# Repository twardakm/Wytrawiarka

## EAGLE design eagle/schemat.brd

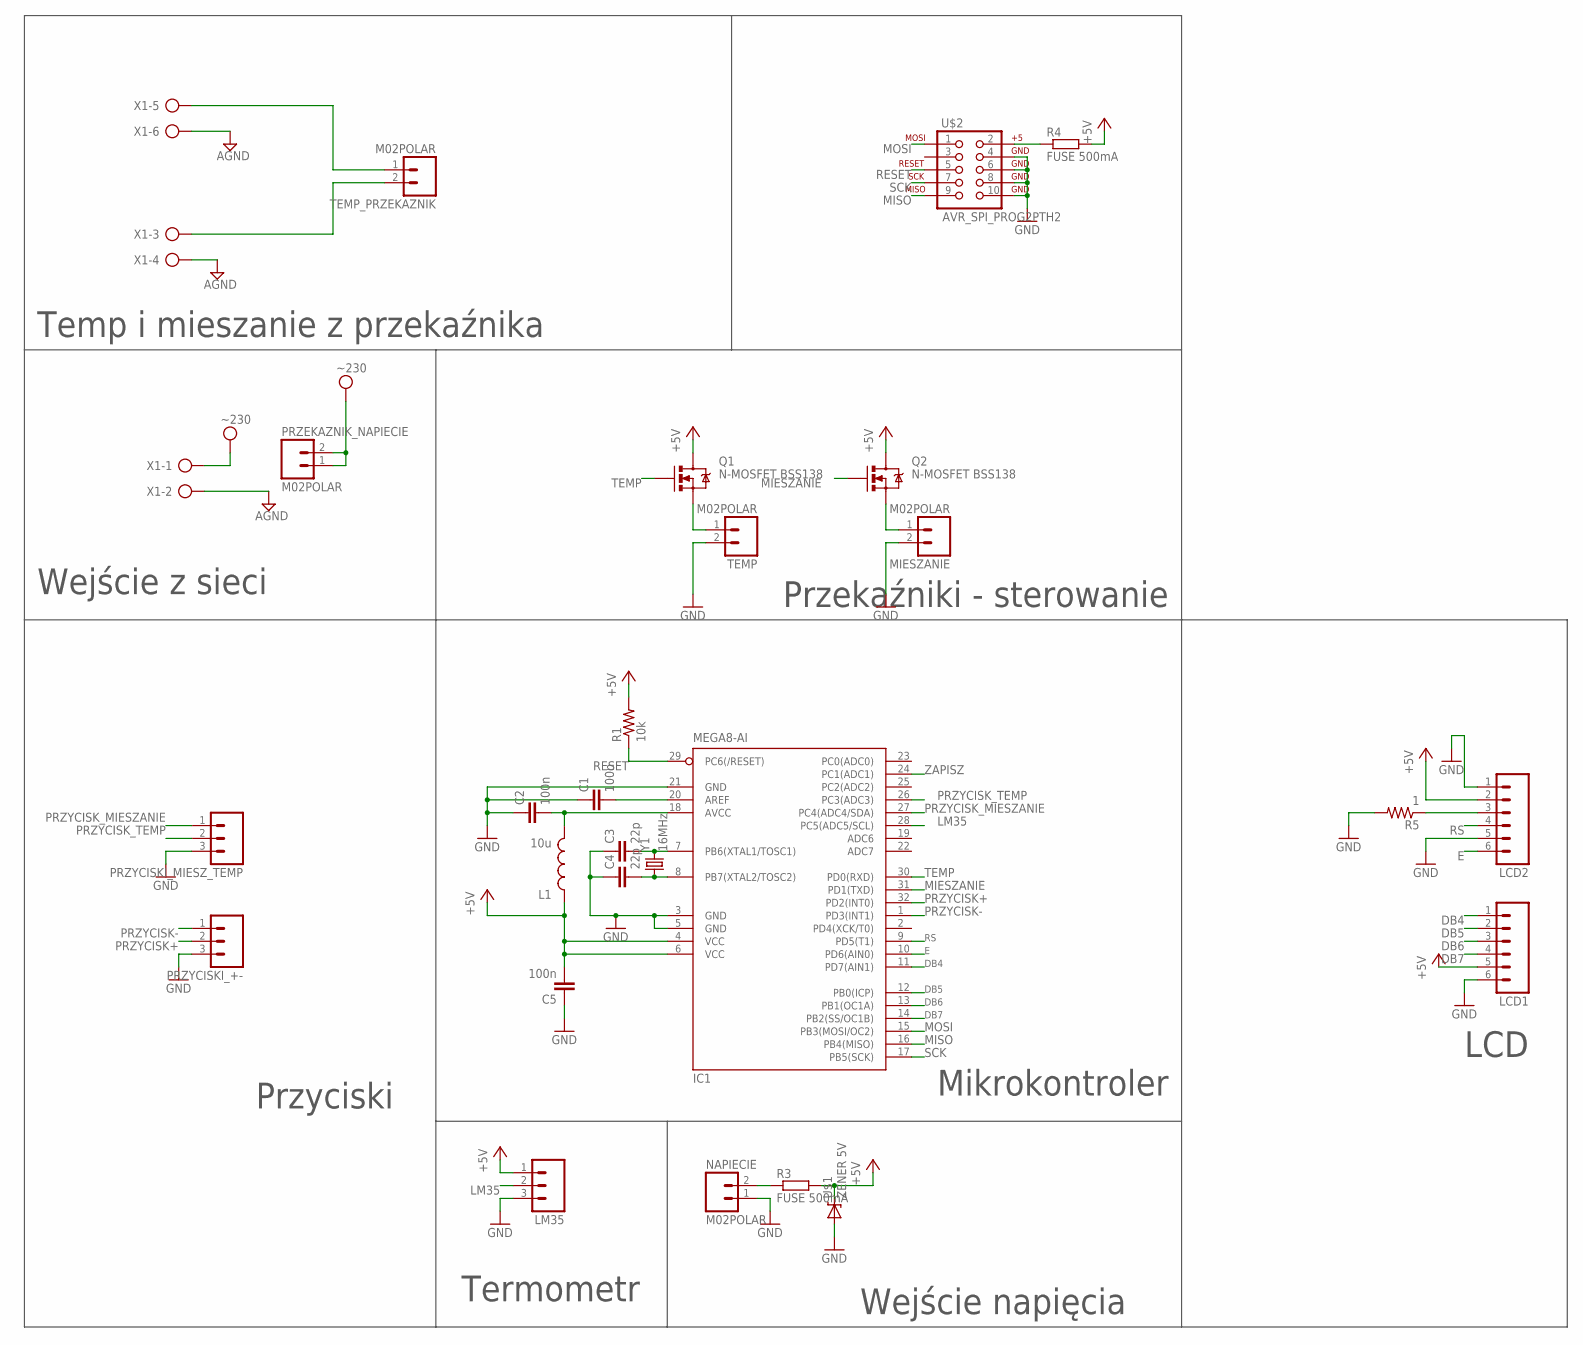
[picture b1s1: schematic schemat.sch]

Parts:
C1, C2, C5: 100n; 0805
C3, C4: 22p; 0805
IC1: MEGA8-AI; TQFP32-08
L1: 10u; 0805
LCD1, LCD2: M06POLAR; MOLEX-1X6
LM35: M03POLAR; MOLEX-1X3
MIESZANIE: M02POLAR; MOLEX-1X2
NAPIECIE: M02POLAR; MOLEX-1X2
PRZEKAZNIK_NAPIECIE: M02POLAR; MOLEX-1X2
PRZYCISKI_+-: M03POLAR; MOLEX-1X3
PRZYCISKI_MIESZ_TEMP: M03POLAR; MOLEX-1X3
Q1, Q2: N-MOSFET BSS138; SOT23
R1: 10k; 0805
R3, R4: FUSE 500mA; M0805
R5: 1; 0805
TEMP: M02POLAR; MOLEX-1X2
TEMP_PRZEKAZNIK: M02POLAR; MOLEX-1X2
U$1: ZENER 5V; SMB-DIODE
U$2: AVR_SPI_PROG2PTH2; 2X5-SHROUDED
X1: AK300/6
Y1: 16MHz; HC49US

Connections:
+5V: C5.2, IC1.4 (VCC), IC1.6 (VCC), L1.1, LCD1.5, LCD2.2, LM35.1, Q1.3 (D), Q2.3 (D), R1.2, R3.2, R4.2, U$1.C
AGND: X1.2, X1.4, X1.6
DB4: IC1.11 (PD7(AIN1)), LCD1.1
DB5: IC1.12 (PB0(ICP)), LCD1.2
DB6: IC1.13 (PB1(OC1A)), LCD1.3
DB7: IC1.14 (PB2(SS/OC1B)), LCD1.4
E: IC1.10 (PD6(AIN0)), LCD2.6
GND: C1.1, C2.1, C3.1, C4.1, C5.1, IC1.3 (GND), IC1.5 (GND), IC1.21 (GND), LCD1.6, LCD2.1, LCD2.5, LM35.3, MIESZANIE.2, NAPIECIE.1, PRZYCISKI_+-.3, PRZYCISKI_MIESZ_TEMP.3, R5.2, TEMP.2, U$1.A, U$2.4, U$2.6, U$2.8, U$2.10
LM35: IC1.28 (PC5(ADC5/SCL)), LM35.2
MIESZANIE: IC1.31 (PD1(TXD)), Q2.1 (G)
MISO: IC1.16 (PB4(MISO)), U$2.9
MOSI: IC1.15 (PB3(MOSI/OC2)), U$2.1
unnamed: C2.2, IC1.18 (AVCC), L1.2
unnamed: C1.2, IC1.20 (AREF)
unnamed: Q1.2 (S), TEMP.1
unnamed: MIESZANIE.1, Q2.2 (S)
unnamed: C4.2, IC1.8 (PB7(XTAL2/TOSC2)), Y1.1
unnamed: C3.2, IC1.7 (PB6(XTAL1/TOSC1)), Y1.2
unnamed: NAPIECIE.2, R3.1
unnamed: TEMP_PRZEKAZNIK.2, X1.3
unnamed: R4.1, U$2.2
unnamed: TEMP_PRZEKAZNIK.1, X1.5
unnamed: LCD2.3, R5.1
PRZYCISK+: IC1.32 (PD2(INT0)), PRZYCISKI_+-.2
PRZYCISK-: IC1.1 (PD3(INT1)), PRZYCISKI_+-.1
PRZYCISK_MIESZANIE: IC1.27 (PC4(ADC4/SDA)), PRZYCISKI_MIESZ_TEMP.1
PRZYCISK_TEMP: IC1.26 (PC3(ADC3)), PRZYCISKI_MIESZ_TEMP.2
RESET: IC1.29 (PC6(/RESET)), R1.1, U$2.5
RS: IC1.9 (PD5(T1)), LCD2.4
SCK: IC1.17 (PB5(SCK)), U$2.7
TEMP: IC1.30 (PD0(RXD)), Q1.1 (G)
VDD: PRZEKAZNIK_NAPIECIE.1, PRZEKAZNIK_NAPIECIE.2, X1.1
ZAPISZ: IC1.24 (PC1(ADC1))

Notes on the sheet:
Mikrokontroler
LCD
Termometr
Przyciski
Przekaźniki - sterowanie
Wejście napięcia
Wejście z sieci
Temp i mieszanie z przekaźnika

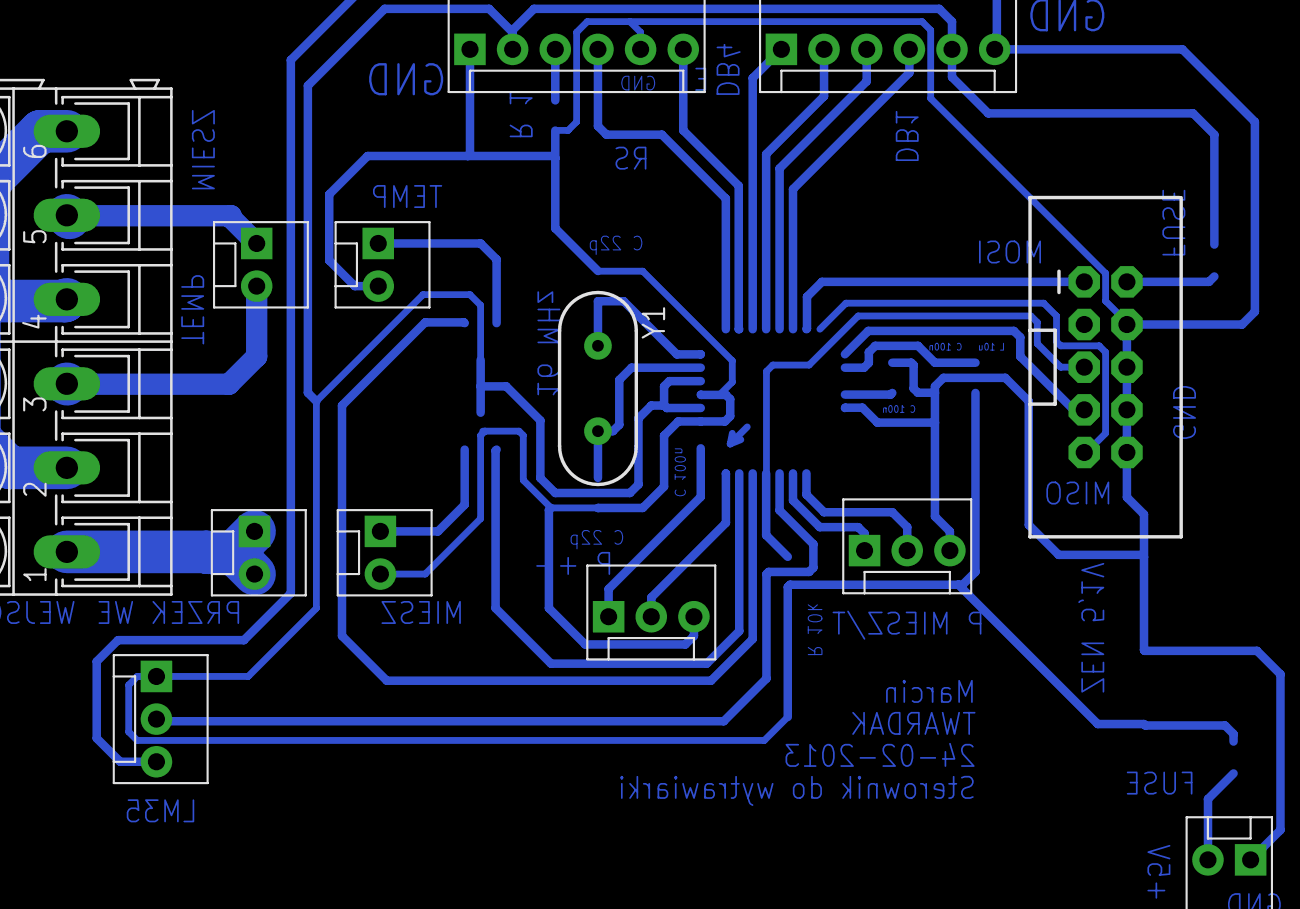
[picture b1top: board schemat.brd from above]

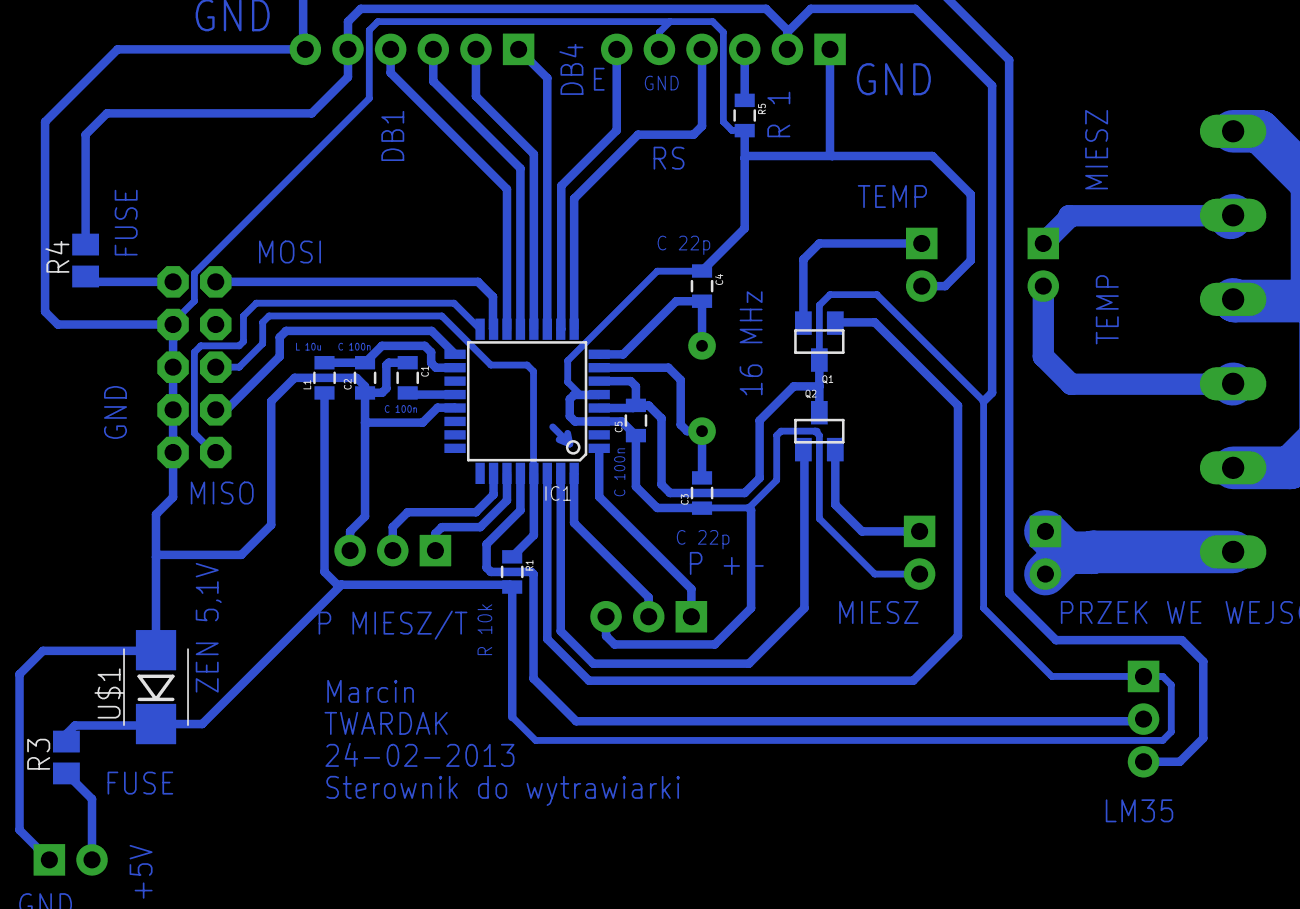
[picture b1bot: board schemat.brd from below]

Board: 2 copper layers, 27 parts (14 on the bottom side), 32 nets.

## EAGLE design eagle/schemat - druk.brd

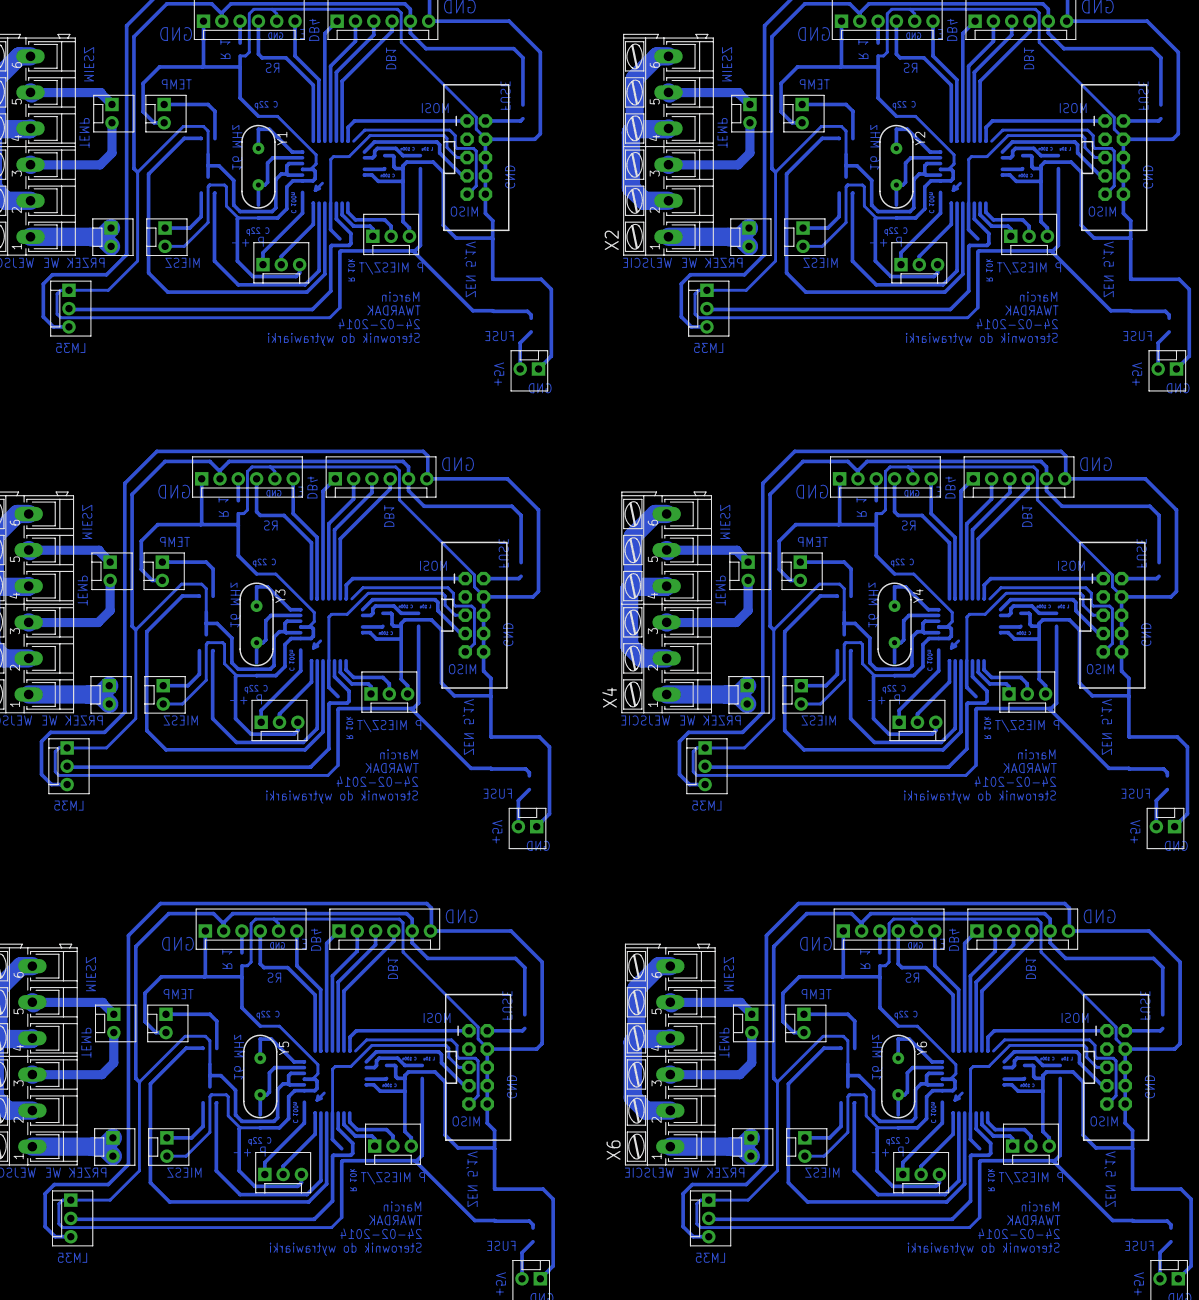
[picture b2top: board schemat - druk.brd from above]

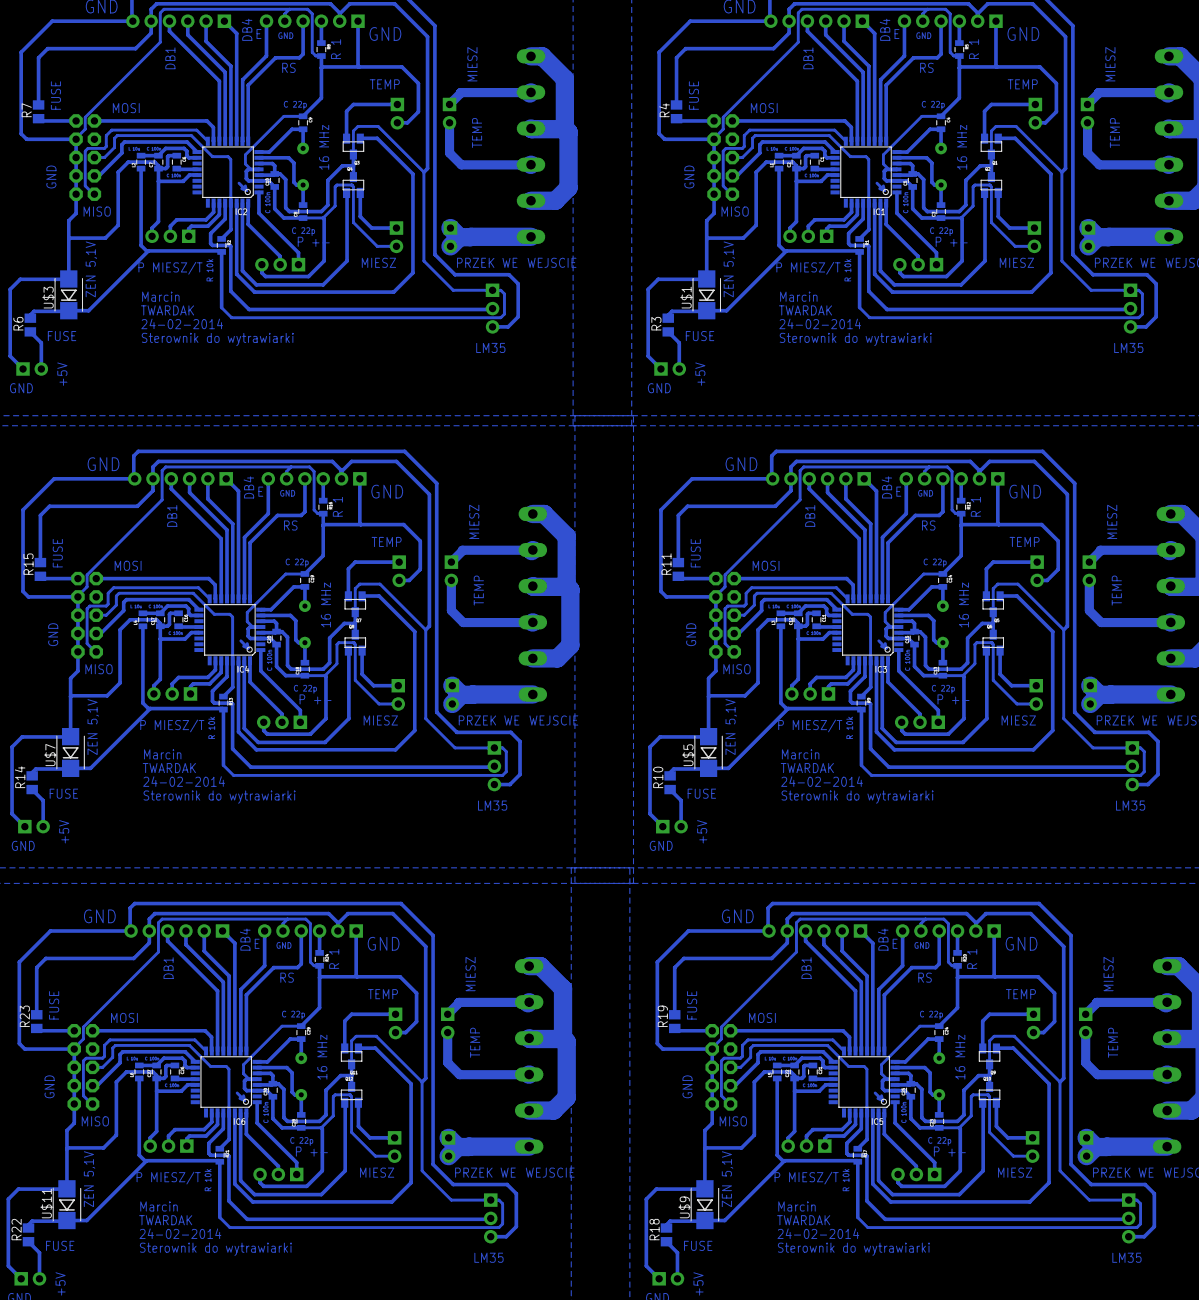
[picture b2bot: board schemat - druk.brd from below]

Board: 2 copper layers, 162 parts (84 on the bottom side), 192 nets.

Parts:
C1, C2, C5, C6, C7, C10, C11, C12, C15, C16, C17, C20, C21, C22, C25, C26, C27, C30: 100n; 0805
C3, C4, C8, C9, C13, C14, C18, C19, C23, C24, C28, C29: 22p; 0805
IC1, IC2, IC3, IC4, IC5, IC6: MEGA8-AI; TQFP32-08
L1, L2, L3, L4, L5, L6: 10u; 0805
LCD1, LCD2, LCD3, LCD4, LCD5, LCD6, LCD7, LCD8, LCD9, LCD10, LCD11, LCD12: MOLEX-1X6
LM1, LM2, LM3, LM4, LM5, LM35: MOLEX-1X3
MIESZANIE, MIESZANIE1, MIESZANIE2, MIESZANIE3, MIESZANIE4, MIESZANIE5: M02POLAR; MOLEX-1X2
NAPIECIE, NAPIECIE1, NAPIECIE2, NAPIECIE3, NAPIECIE4, NAPIECIE5: M02POLAR; MOLEX-1X2
PRZEKAZNIK_NAPIECIE, PRZEKAZNIK_NAPIECIE1, PRZEKAZNIK_NAPIECIE2, PRZEKAZNIK_NAPIECIE3, PRZEKAZNIK_NAPIECIE4, PRZEKAZNIK_NAPIECIE5: M02POLAR; MOLEX-1X2
PRZYCISKI_+-, PRZYCISKI_+-1, PRZYCISKI_+-2, PRZYCISKI_+-3, PRZYCISKI_+-4, PRZYCISKI_+-5: MOLEX-1X3
PRZYCISKI_MIESZ_TEMP, PRZYCISKI_MIESZ_TEMP1, PRZYCISKI_MIESZ_TEMP2, PRZYCISKI_MIESZ_TEMP3, PRZYCISKI_MIESZ_TEMP4, PRZYCISKI_MIESZ_TEMP5: MOLEX-1X3
Q1, Q2, Q3, Q4, Q5, Q6, Q7, Q8, Q9, Q10, Q11, Q12: N-MOSFET BSS138; SOT23
R1, R2, R9, R13, R17, R21: 10k; 0805
R3, R4, R6, R7, R10, R11, R14, R15, R18, R19, R22, R23: FUSE 500mA; M0805
R5, R8, R12, R16, R20, R24: 1; 0805
TEMP, TEMP1, TEMP2, TEMP3, TEMP4, TEMP5: M02POLAR; MOLEX-1X2
TEMP_PRZEKAZNIK, TEMP_PRZEKAZNIK1, TEMP_PRZEKAZNIK2, TEMP_PRZEKAZNIK3, TEMP_PRZEKAZNIK4, TEMP_PRZEKAZNIK5: M02POLAR; MOLEX-1X2
U$1, U$3, U$5, U$7, U$9, U$11: ZENER 5V; SMB-DIODE
U$2, U$4, U$6, U$8, U$10, U$12: AVR_SPI_PROG2PTH2; 2X5-SHROUDED
X1, X2, X3, X4, X5, X6: AK300/6
Y1, Y2, Y3, Y4, Y5, Y6: 16MHz; HC49US

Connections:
+5V: C5.2, IC1.4, IC1.6, L1.1, LCD1.5, LCD2.2, LM35.1, Q1.3, Q2.3, R1.2, R3.2, R4.2, U$1.C
+5V1: C10.2, IC2.4, IC2.6, L2.1, LCD3.5, LCD4.2, LM1.1, Q3.3, Q4.3, R2.2, R6.2, R7.2, U$3.C
+5V2: C15.2, IC3.4, IC3.6, L3.1, LCD5.5, LCD6.2, LM2.1, Q5.3, Q6.3, R9.2, R10.2, R11.2, U$5.C
+5V3: C20.2, IC4.4, IC4.6, L4.1, LCD7.5, LCD8.2, LM3.1, Q7.3, Q8.3, R13.2, R14.2, R15.2, U$7.C
+5V4: C25.2, IC5.4, IC5.6, L5.1, LCD9.5, LCD10.2, LM4.1, Q9.3, Q10.3, R17.2, R18.2, R19.2, U$9.C
+5V5: C30.2, IC6.4, IC6.6, L6.1, LCD11.5, LCD12.2, LM5.1, Q11.3, Q12.3, R21.2, R22.2, R23.2, U$11.C
AGND: X1.2, X1.4, X1.6
AGND1: X2.2, X2.4, X2.6
AGND2: X3.2, X3.4, X3.6
AGND3: X4.2, X4.4, X4.6
AGND4: X5.2, X5.4, X5.6
AGND5: X6.2, X6.4, X6.6
DB1: IC2.11, LCD3.1
DB2: IC2.12, LCD3.2
DB3: IC2.13, LCD3.3
DB4: IC1.11, LCD1.1
DB5: IC1.12, LCD1.2
DB6: IC1.13, LCD1.3
DB7: IC1.14, LCD1.4
DB8: IC2.14, LCD3.4
DB9: IC3.11, LCD5.1
DB10: IC3.12, LCD5.2
DB11: IC3.13, LCD5.3
DB12: IC3.14, LCD5.4
DB13: IC4.11, LCD7.1
DB14: IC4.12, LCD7.2
DB15: IC4.13, LCD7.3
DB16: IC4.14, LCD7.4
DB17: IC5.11, LCD9.1
DB18: IC5.12, LCD9.2
DB19: IC5.13, LCD9.3
DB20: IC5.14, LCD9.4
DB21: IC6.11, LCD11.1
DB22: IC6.12, LCD11.2
DB23: IC6.13, LCD11.3
DB24: IC6.14, LCD11.4
E: IC1.10, LCD2.6
E1: IC2.10, LCD4.6
E2: IC3.10, LCD6.6
E3: IC4.10, LCD8.6
E4: IC5.10, LCD10.6
E5: IC6.10, LCD12.6
GND: C1.1, C2.1, C3.1, C4.1, C5.1, IC1.3, IC1.5, IC1.21, LCD1.6, LCD2.1, LCD2.5, LM35.3, MIESZANIE.2, NAPIECIE.1, PRZYCISKI_+-.3, PRZYCISKI_MIESZ_TEMP.3, R5.2, TEMP.2, U$1.A, U$2.4, U$2.6, U$2.8, U$2.10
GND1: C6.1, C7.1, C8.1, C9.1, C10.1, IC2.3, IC2.5, IC2.21, LCD3.6, LCD4.1, LCD4.5, LM1.3, MIESZANIE1.2, NAPIECIE1.1, PRZYCISKI_+-1.3, PRZYCISKI_MIESZ_TEMP1.3, R8.2, TEMP1.2, U$3.A, U$4.4, U$4.6, U$4.8, U$4.10
GND2: C11.1, C12.1, C13.1, C14.1, C15.1, IC3.3, IC3.5, IC3.21, LCD5.6, LCD6.1, LCD6.5, LM2.3, MIESZANIE2.2, NAPIECIE2.1, PRZYCISKI_+-2.3, PRZYCISKI_MIESZ_TEMP2.3, R12.2, TEMP2.2, U$5.A, U$6.4, U$6.6, U$6.8, U$6.10
GND3: C16.1, C17.1, C18.1, C19.1, C20.1, IC4.3, IC4.5, IC4.21, LCD7.6, LCD8.1, LCD8.5, LM3.3, MIESZANIE3.2, NAPIECIE3.1, PRZYCISKI_+-3.3, PRZYCISKI_MIESZ_TEMP3.3, R16.2, TEMP3.2, U$7.A, U$8.4, U$8.6, U$8.8, U$8.10
GND4: C21.1, C22.1, C23.1, C24.1, C25.1, IC5.3, IC5.5, IC5.21, LCD9.6, LCD10.1, LCD10.5, LM4.3, MIESZANIE4.2, NAPIECIE4.1, PRZYCISKI_+-4.3, PRZYCISKI_MIESZ_TEMP4.3, R20.2, TEMP4.2, U$9.A, U$10.4, U$10.6, U$10.8, U$10.10
GND5: C26.1, C27.1, C28.1, C29.1, C30.1, IC6.3, IC6.5, IC6.21, LCD11.6, LCD12.1, LCD12.5, LM5.3, MIESZANIE5.2, NAPIECIE5.1, PRZYCISKI_+-5.3, PRZYCISKI_MIESZ_TEMP5.3, R24.2, TEMP5.2, U$11.A, U$12.4, U$12.6, U$12.8, U$12.10
LM1: IC2.28, LM1.2
LM2: IC3.28, LM2.2
LM3: IC4.28, LM3.2
LM4: IC5.28, LM4.2
LM5: IC6.28, LM5.2
LM35: IC1.28, LM35.2
MIESZANIE: IC1.31, Q2.1
MIESZANIE1: IC2.31, Q4.1
MIESZANIE2: IC3.31, Q6.1
MIESZANIE3: IC4.31, Q8.1
MIESZANIE4: IC5.31, Q10.1
MIESZANIE5: IC6.31, Q12.1
MISO: IC1.16, U$2.9
MISO1: IC2.16, U$4.9
MISO2: IC3.16, U$6.9
MISO3: IC4.16, U$8.9
MISO4: IC5.16, U$10.9
MISO5: IC6.16, U$12.9
MOSI: IC1.15, U$2.1
MOSI1: IC2.15, U$4.1
MOSI2: IC3.15, U$6.1
MOSI3: IC4.15, U$8.1
MOSI4: IC5.15, U$10.1
MOSI5: IC6.15, U$12.1
unnamed: C2.2, IC1.18, L1.2
unnamed: C1.2, IC1.20
unnamed: Q1.2, TEMP.1
unnamed: MIESZANIE.1, Q2.2
unnamed: C4.2, IC1.8, Y1.1
unnamed: C3.2, IC1.7, Y1.2
unnamed: NAPIECIE.2, R3.1
unnamed: C7.2, IC2.18, L2.2
unnamed: TEMP_PRZEKAZNIK.2, X1.3
unnamed: R4.1, U$2.2
unnamed: C6.2, IC2.20
unnamed: C9.2, IC2.8, Y2.1
unnamed: TEMP_PRZEKAZNIK.1, X1.5
unnamed: C8.2, IC2.7, Y2.2
unnamed: LCD2.3, R5.1
unnamed: Q3.2, TEMP1.1
unnamed: MIESZANIE1.1, Q4.2
unnamed: TEMP_PRZEKAZNIK1.1, X2.5
unnamed: NAPIECIE1.2, R6.1
unnamed: TEMP_PRZEKAZNIK1.2, X2.3
unnamed: R7.1, U$4.2
unnamed: LCD4.3, R8.1
unnamed: C12.2, IC3.18, L3.2
unnamed: C11.2, IC3.20
unnamed: C14.2, IC3.8, Y3.1
unnamed: C13.2, IC3.7, Y3.2
unnamed: Q5.2, TEMP2.1
unnamed: MIESZANIE2.1, Q6.2
unnamed: TEMP_PRZEKAZNIK2.1, X3.5
unnamed: NAPIECIE2.2, R10.1
unnamed: TEMP_PRZEKAZNIK2.2, X3.3
unnamed: R11.1, U$6.2
unnamed: LCD6.3, R12.1
unnamed: C17.2, IC4.18, L4.2
unnamed: C16.2, IC4.20
unnamed: C19.2, IC4.8, Y4.1
unnamed: C18.2, IC4.7, Y4.2
unnamed: Q7.2, TEMP3.1
unnamed: MIESZANIE3.1, Q8.2
unnamed: TEMP_PRZEKAZNIK3.1, X4.5
unnamed: NAPIECIE3.2, R14.1
unnamed: TEMP_PRZEKAZNIK3.2, X4.3
unnamed: R15.1, U$8.2
unnamed: LCD8.3, R16.1
unnamed: C22.2, IC5.18, L5.2
unnamed: C21.2, IC5.20
unnamed: C24.2, IC5.8, Y5.1
unnamed: C23.2, IC5.7, Y5.2
unnamed: Q9.2, TEMP4.1
unnamed: MIESZANIE4.1, Q10.2
unnamed: TEMP_PRZEKAZNIK4.1, X5.5
unnamed: NAPIECIE4.2, R18.1
unnamed: TEMP_PRZEKAZNIK4.2, X5.3
unnamed: R19.1, U$10.2
unnamed: LCD10.3, R20.1
unnamed: C27.2, IC6.18, L6.2
unnamed: C26.2, IC6.20
unnamed: C29.2, IC6.8, Y6.1
unnamed: C28.2, IC6.7, Y6.2
unnamed: Q11.2, TEMP5.1
unnamed: MIESZANIE5.1, Q12.2
unnamed: TEMP_PRZEKAZNIK5.1, X6.5
unnamed: NAPIECIE5.2, R22.1
unnamed: TEMP_PRZEKAZNIK5.2, X6.3
unnamed: R23.1, U$12.2
unnamed: LCD12.3, R24.1
PRZYCISK+: IC1.32, PRZYCISKI_+-.2
PRZYCISK+1: IC2.32, PRZYCISKI_+-1.2
PRZYCISK+2: IC3.32, PRZYCISKI_+-2.2
PRZYCISK+3: IC4.32, PRZYCISKI_+-3.2
PRZYCISK+4: IC5.32, PRZYCISKI_+-4.2
PRZYCISK+5: IC6.32, PRZYCISKI_+-5.2
PRZYCISK-: IC1.1, PRZYCISKI_+-.1
PRZYCISK-1: IC2.1, PRZYCISKI_+-1.1
PRZYCISK-2: IC3.1, PRZYCISKI_+-2.1
PRZYCISK-3: IC4.1, PRZYCISKI_+-3.1
PRZYCISK-4: IC5.1, PRZYCISKI_+-4.1
PRZYCISK-5: IC6.1, PRZYCISKI_+-5.1
PRZYCISK_MIESZANIE: IC1.27, PRZYCISKI_MIESZ_TEMP.1
PRZYCISK_MIESZANIE1: IC2.27, PRZYCISKI_MIESZ_TEMP1.1
PRZYCISK_MIESZANIE2: IC3.27, PRZYCISKI_MIESZ_TEMP2.1
PRZYCISK_MIESZANIE3: IC4.27, PRZYCISKI_MIESZ_TEMP3.1
PRZYCISK_MIESZANIE4: IC5.27, PRZYCISKI_MIESZ_TEMP4.1
PRZYCISK_MIESZANIE5: IC6.27, PRZYCISKI_MIESZ_TEMP5.1
PRZYCISK_TEMP: IC1.26, PRZYCISKI_MIESZ_TEMP.2
PRZYCISK_TEMP1: IC2.26, PRZYCISKI_MIESZ_TEMP1.2
PRZYCISK_TEMP2: IC3.26, PRZYCISKI_MIESZ_TEMP2.2
PRZYCISK_TEMP3: IC4.26, PRZYCISKI_MIESZ_TEMP3.2
PRZYCISK_TEMP4: IC5.26, PRZYCISKI_MIESZ_TEMP4.2
PRZYCISK_TEMP5: IC6.26, PRZYCISKI_MIESZ_TEMP5.2
RESET: IC1.29, R1.1, U$2.5
RESET1: IC2.29, R2.1, U$4.5
RESET2: IC3.29, R9.1, U$6.5
RESET3: IC4.29, R13.1, U$8.5
RESET4: IC5.29, R17.1, U$10.5
RESET5: IC6.29, R21.1, U$12.5
RS: IC1.9, LCD2.4
RS1: IC2.9, LCD4.4
RS2: IC3.9, LCD6.4
RS3: IC4.9, LCD8.4
RS4: IC5.9, LCD10.4
RS5: IC6.9, LCD12.4
SCK: IC1.17, U$2.7
SCK1: IC2.17, U$4.7
SCK2: IC3.17, U$6.7
SCK3: IC4.17, U$8.7
SCK4: IC5.17, U$10.7
SCK5: IC6.17, U$12.7
TEMP: IC1.30, Q1.1
TEMP1: IC2.30, Q3.1
TEMP2: IC3.30, Q5.1
TEMP3: IC4.30, Q7.1
TEMP4: IC5.30, Q9.1
TEMP5: IC6.30, Q11.1
VDD: PRZEKAZNIK_NAPIECIE.1, PRZEKAZNIK_NAPIECIE.2, X1.1
VDD1: PRZEKAZNIK_NAPIECIE1.1, PRZEKAZNIK_NAPIECIE1.2, X2.1
VDD2: PRZEKAZNIK_NAPIECIE2.1, PRZEKAZNIK_NAPIECIE2.2, X3.1
VDD3: PRZEKAZNIK_NAPIECIE3.1, PRZEKAZNIK_NAPIECIE3.2, X4.1
VDD4: PRZEKAZNIK_NAPIECIE4.1, PRZEKAZNIK_NAPIECIE4.2, X5.1
VDD5: PRZEKAZNIK_NAPIECIE5.1, PRZEKAZNIK_NAPIECIE5.2, X6.1

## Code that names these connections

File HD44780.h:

#ifndef _HD44780
#define _HD44780
//-------------------------------------------------------------------------------------------------
// Wywietlacz alfanumeryczny ze sterownikiem HD44780
// Sterowanie w trybie 4-bitowym bez odczytu flagi zajêtoci
// z dowolnym przypisaniem sygna³ów steruj¹cych
// Plik : HD44780.h
// Mikrokontroler : Atmel AVR
// Kompilator : avr-gcc
// Autor : Rados³aw Kwiecieñ
// ród³o : http://radzio.dxp.pl/hd44780/
// Data : 24.03.2007
//-------------------------------------------------------------------------------------------------

#include <avr/io.h>
#include <util/delay.h>

//-------------------------------------------------------------------------------------------------
//
// Konfiguracja sygna³ów steruj¹cych wywietlaczem.
// Mo¿na zmieniæ stosownie do potrzeb.
//
//-------------------------------------------------------------------------------------------------
#define LCD_RS_DIR		DDRD
#define LCD_RS_PORT 	PORTD
#define LCD_RS			(1 << PD5)

#define LCD_E_DIR		DDRD
#define LCD_E_PORT		PORTD
#define LCD_E			(1 << PD6)

#define LCD_DB4_DIR		DDRD
#define LCD_DB4_PORT	PORTD
#define LCD_DB4			(1 << PD7)

#define LCD_DB5_DIR		DDRB
#define LCD_DB5_PORT	PORTB
#define LCD_DB5			(1 << PB0)

#define LCD_DB6_DIR		DDRB
#define LCD_DB6_PORT	PORTB
#define LCD_DB6			(1 << PB1)

#define LCD_DB7_DIR		DDRB
#define LCD_DB7_PORT	PORTB
#define LCD_DB7			(1 << PB2)

//-------------------------------------------------------------------------------------------------
//
// Instrukcje kontrolera Hitachi HD44780
//
//-------------------------------------------------------------------------------------------------

#define HD44780_CLEAR					0x01

#define HD44780_HOME					0x02

#define HD44780_ENTRY_MODE				0x04
	#define HD44780_EM_SHIFT_CURSOR		0
	#define HD44780_EM_SHIFT_DISPLAY	1
	#define HD44780_EM_DECREMENT		0
	#define HD44780_EM_INCREMENT		2

#define HD44780_DISPLAY_ONOFF			0x08
	#define HD44780_DISPLAY_OFF			0
	#define HD44780_DISPLAY_ON			4
	#define HD44780_CURSOR_OFF			0
	#define HD44780_CURSOR_ON			2
	#define HD44780_CURSOR_NOBLINK		0
	#define HD44780_CURSOR_BLINK		1

#define HD44780_DISPLAY_CURSOR_SHIFT	0x10
	#define HD44780_SHIFT_CURSOR		0
	#define HD44780_SHIFT_DISPLAY		8
	#define HD44780_SHIFT_LEFT			0
	#define HD44780_SHIFT_RIGHT			4

#define HD44780_FUNCTION_SET			0x20
	#define HD44780_FONT5x8				0
	#define HD44780_FONT5x10			4
	#define HD44780_ONE_LINE			0
	#define HD44780_TWO_LINE			8
	#define HD44780_4_BIT				0
	#define HD44780_8_BIT				16

#define HD44780_CGRAM_SET				0x40

#define HD44780_DDRAM_SET				0x80

//-------------------------------------------------------------------------------------------------
//
// Deklaracje funkcji
//
//-------------------------------------------------------------------------------------------------

void LCD_WriteCommand(unsigned char);
void LCD_WriteData(unsigned char);
void LCD_WriteText(char *);
void LCD_GoTo(unsigned char, unsigned char);
void LCD_Clear(void);
void LCD_Home(void);
void LCD_Initalize(void);

//Marcin Twardak
char * Int_to_char(int i, int lenght);
void LCD_Tekst_startowy();

//-------------------------------------------------------------------------------------------------
//
// Koniec pliku HD44780.h
//
//-------------------------------------------------------------------------------------------------
#endif // _HD44780

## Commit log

2014-02-02 Pierwszy commit
2014-02-02 Dodane pliki HD44780
    Źródło plików: http://radzio.dxp.pl
2014-02-02 Wyświetlanie 2 linii na wyświetlaczu
2014-02-02 Wyświetla prosty pomiar temp
2014-02-02 Wyświetlanie temp z odpowiednio ustawionym prescalerem
2014-02-02 funkcja konwersji int na char*
2014-02-02 Porządne wyświetlanie temperatury
2014-02-02 Inicjowanie wartości domyślnych
2014-02-02 Zmiana wartości parametrów
2014-02-02 Elegancka zmiana wartości parametrów
2014-02-02 Działa sterowanie temperatur
2014-02-02 Działa mieszanie z najprostszym algorytmem
2014-02-03 Sprawdzenie stanu przycisku zapisz
2014-02-03 Skończony program, gotowy do wgrania
2014-02-03 Layout
2014-02-04 Schemat eagle
2014-02-05 Gotowa płytka
2014-02-05 do wydruku
2014-02-07 Poprawiony schemat
    Nie dało się przylutować microUSB (zła biblioteka)
    Nie podłączony RESET
2014-02-07 Schemat do druku
2014-02-07 uzupełniony opis schematu
2014-02-07 Dodane opisy + wersja do druku
2014-02-08 kolejne poprawki
2014-03-02 Zmieniony schemat + zmiany w programie
2014-03-02 Poprawiony program do nowego schematu
    trzeba dopisać zapisywanie
2014-03-02 Poprawiony ADC

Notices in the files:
parts and their libraries:
SparkFun-Passives: Licensing: CC v3.0 Share-Alike You are welcome to use this library for commercial purposes.
